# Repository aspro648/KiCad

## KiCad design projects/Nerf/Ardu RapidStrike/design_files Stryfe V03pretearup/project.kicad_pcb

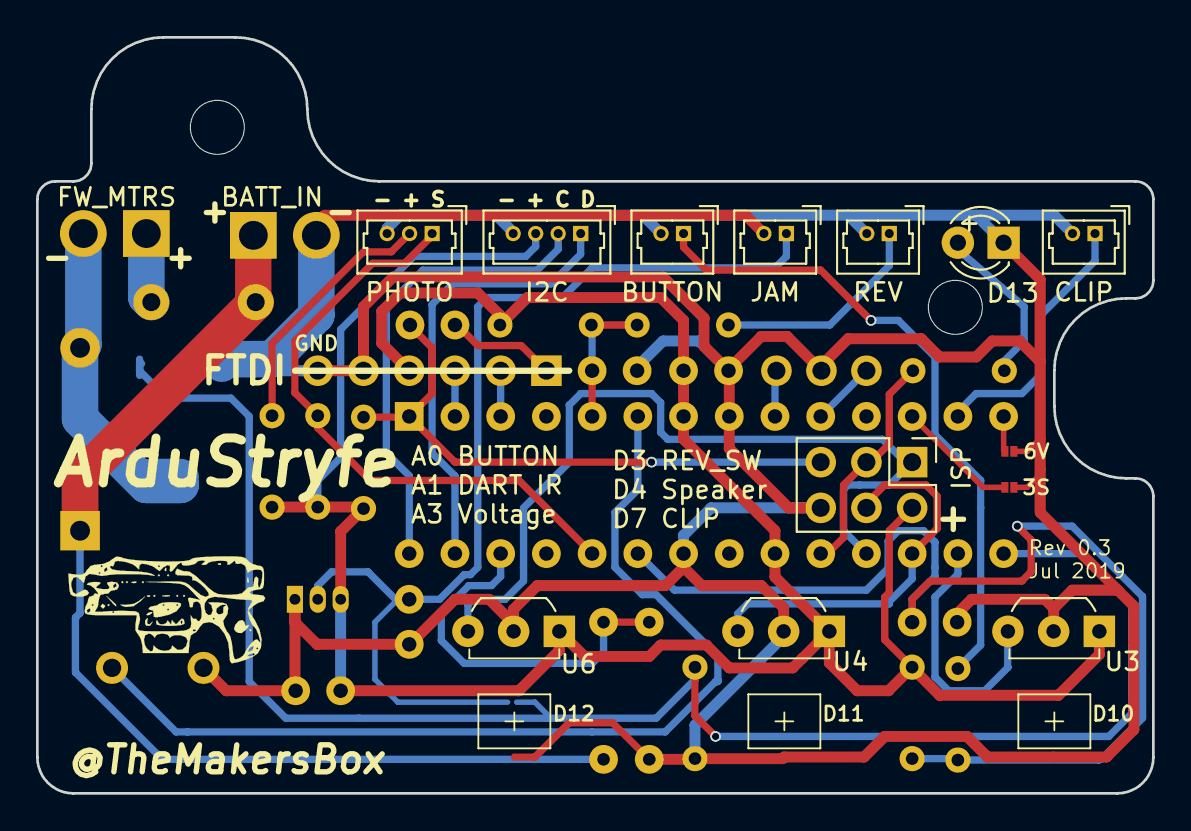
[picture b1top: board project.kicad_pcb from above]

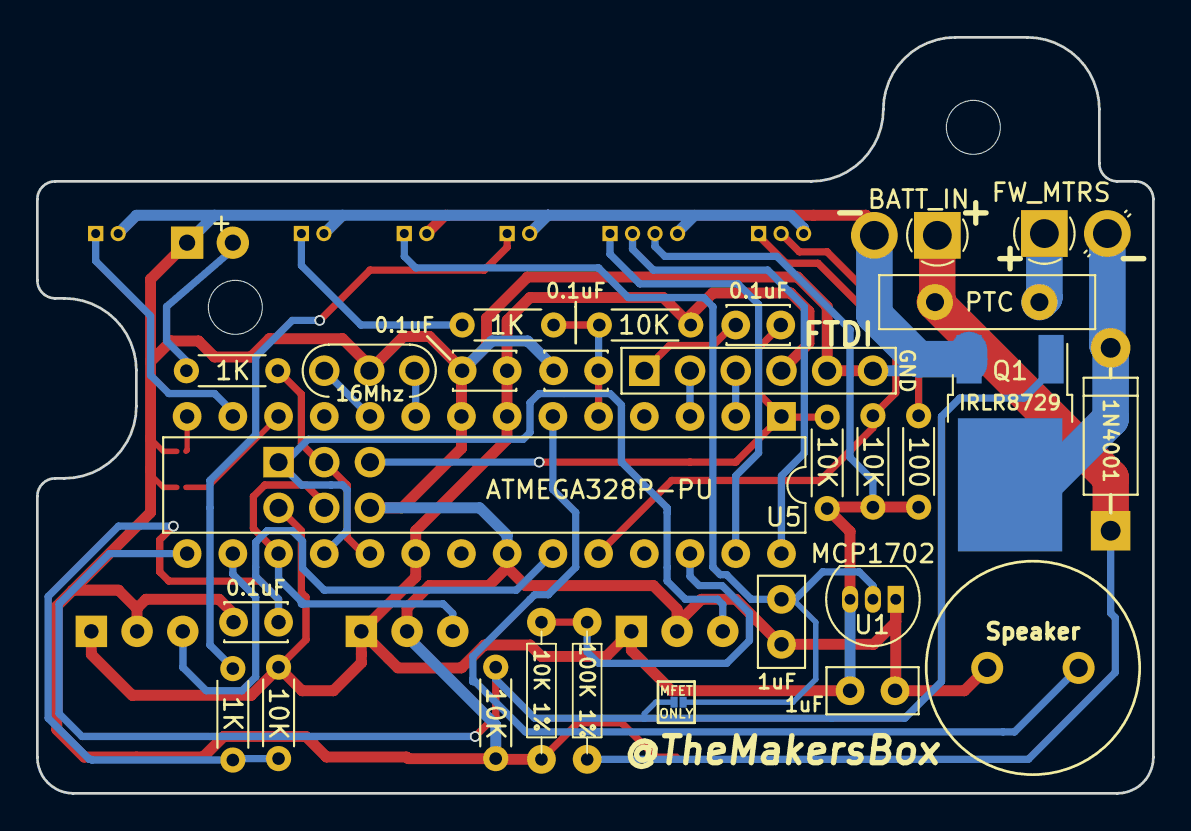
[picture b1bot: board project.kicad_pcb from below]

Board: 2 copper layers, 62.0 x 42.0 mm, 43 parts (28 on the bottom side), 31 nets.

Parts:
C1, C4: 1uF; C_Disc_D5.0mm_W2.5mm_P2.50mm
C5, C7, C9, C10: 0.1uF; C_Disc_D3.4mm_W2.1mm_P2.50mm
CON1: ISP; Pin_Header_Straight_2x03_Pitch2.54mm
D1: 1N4001; D_DO-41
D2: D13; LED_D3.0mm
F1: PTC; Fuse_Littelfuse-LVR125
J1: JAM; Molex_PicoBlade_53047-0210_02x1.25mm_Straight
J2: BATT_IN; TerminalBlock_P3.50mm_Horizontal
J5: I2C; Molex_PicoBlade_53047-0410_04x1.25mm_Straight
J6: REV; Molex_PicoBlade_53047-0210_02x1.25mm_Straight
J7: FTDI; Pin_Header_Straight_1x06_Pitch2.54mm
J8: PHOTO; Molex_PicoBlade_53047-0310_03x1.25mm_Straight
J9: FW_MTRS; TerminalBlock_P3.50mm_Horizontal
J12: CLIP; Molex_PicoBlade_53047-0210_02x1.25mm_Straight
J14, J14#2: NPTH; SolderWirePad_single_2-5mmDrill
J21: BUTTON; Molex_PicoBlade_53047-0210_02x1.25mm_Straight
JP1: 6V; JMP
JP2: 3S; JMP
JP3: MOSFET_ONLY; JMP
LS1: Speaker; SPEAKER
Q1: IRLR8729; TO-252-2_hand_soldering
R2, R7, R18: 1K; R__P5.08mm
R6, R9, R17, R19, R20: 10K; R__P5.08mm
R8: 100K 1%; R_7.5mm
R12: 10K 1%; R_7.5mm
R21: 100; R__P5.08mm
U1: MCP1702; TO-92_Inline_Narrow_Oval
U3, U4, U6: HALL SENSOR; Hall_Sensor
U5: ATMEGA328P-PU; DIP-28_W7.62mm
Y1: 16Mhz; Resonator-3pin_w7.0mm_h2.5mm

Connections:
/0(Rx): J7.3, U5.2
/1(Tx): J7.2, U5.3
/3(**): C7.1, R6.1, R7.2, U5.5
/4: LS1.1, U5.6
/6(**): JP2.1, U5.12
/7: J12.1, U5.13
/8: JP1.1, U5.14
/9(**): JP3.2, Q1.1, R9.2, U5.15
/10(SS): U3.3, U5.16
/11(MOSI): CON1.4, U4.3, U5.17
/12(MISO): CON1.1, U5.18, U6.3
/13(SCK): CON1.3, R2.1, U5.19
/#RTS: C9.1, J7.1
/A0: C10.1, R18.2, R19.1, U5.23
/A1: J8.1, R20.2, U5.24
/A3: R8.1, R12.1, U5.26
/A4(SDA): J5.1, U5.27
/A5(SCL): J5.2, U5.28
/BATT: D1.1, F1.1, J1.2, J2.1, R8.2
/Reset: C9.2, CON1.5, R17.1, U5.1
GND: C1.2, C4.2, C5.2, C7.2, C10.2, CON1.6, D2.1, J2.2, J5.4, J6.2, J7.5, J7.6, J8.3, J12.2, J21.2, JP1.2, JP2.2, LS1.2, Q1.3, R9.1, R12.2, U1.1, U3.2, U4.2, U5.8, U5.22, U6.2, Y1.2
unnamed: C1.1, J1.1, JP3.1, U1.2
unnamed: D1.2, J9.2, Q1.2
unnamed: D2.2, R2.2
unnamed: F1.2, J9.1
unnamed: J6.1, R7.1
unnamed: J8.2, R21.2
unnamed: J21.1, R18.1
unnamed: U5.9, Y1.3
unnamed: U5.10, Y1.1
VCC: C4.1, C5.1, CON1.2, J5.3, J7.4, R6.2, R17.2, R19.2, R20.1, R21.1, U1.3, U3.1, U4.1, U5.7, U5.20, U6.1

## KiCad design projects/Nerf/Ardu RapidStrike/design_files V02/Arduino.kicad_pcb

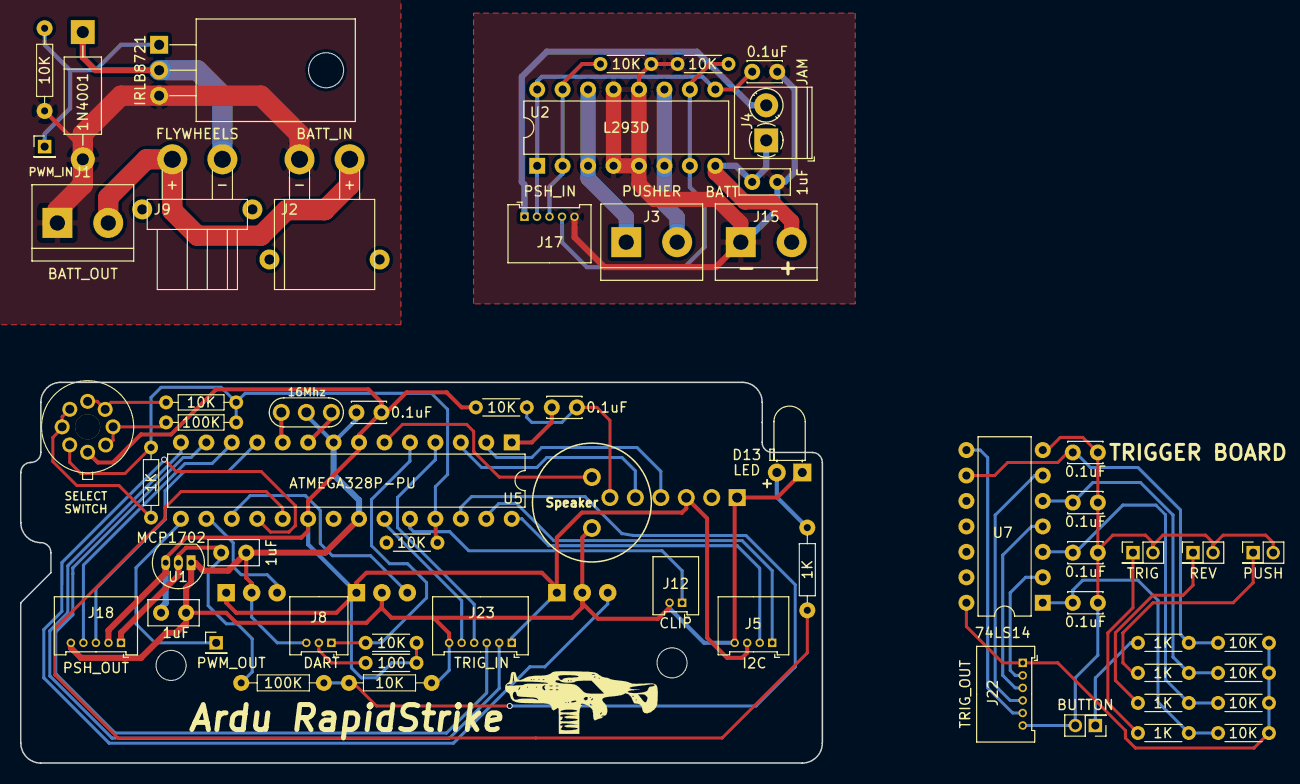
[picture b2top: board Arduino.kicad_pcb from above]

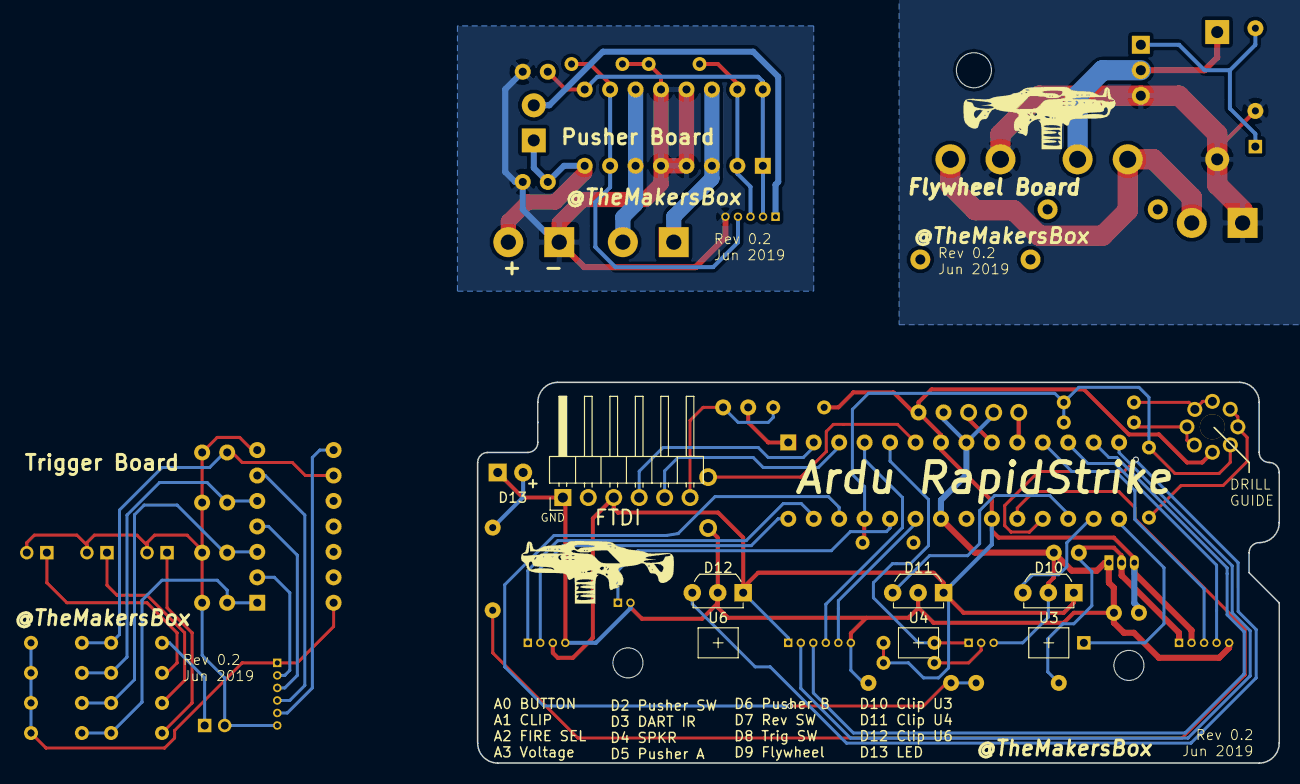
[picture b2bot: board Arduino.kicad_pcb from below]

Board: 2 copper layers, 80.0 x 38.0 mm, 67 parts (4 on the bottom side), 52 nets.

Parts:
C1, C2, C4: 1uF; C_Disc_D5.0mm_W2.5mm_P2.50mm
C3, C5, C6, C7, C8, C9, C10: 0.1uF; C_Disc_D3.4mm_W2.1mm_P2.50mm
D1: 1N4001; D_DO-15_P12.70mm_Horizontal
D2: D13; LED_D3.0mm_Horizontal_O1.27mm_Z10.0mm
J1: BATT_OUT; TerminalBlock_bornier-2_P5.08mm
J2: BATT_IN; XT30PW_M
J3: PUSHER; TerminalBlock_bornier-2_P5.08mm
J4: JAM; TerminalBlock_Phoenix_PT-1,5-2-3.5-H_1x02_P3.50mm_Horizontal
J5: I2C; Molex_PicoBlade_53048-0410_04x1.25mm_Angled
J6: REV; Pin_Header_Straight_2x01_Pitch2.00mm
J7: FTDI; Pin_Header_Angled_1x06_Pitch2.54mm
J8: DART; Molex_PicoBlade_53048-0310_03x1.25mm_Angled
J9: FLYWHEELS; XT30PW_F
J10: PWM_IN; Pin_Header_Straight_1x01_Pitch2.00mm
J11: PWM_OUT; Pin_Header_Straight_1x01_Pitch2.00mm
J12: CLIP; Molex_PicoBlade_53048-0210_02x1.25mm_Angled
J13, J14, J16: NPTH; SolderWirePad_single_2-5mmDrill
J15: BATT; TerminalBlock_bornier-2_P5.08mm
J17: PSH_IN; Molex_PicoBlade_53048-0510_05x1.25mm_Angled
J18: PSH_OUT; Molex_PicoBlade_53048-0510_05x1.25mm_Angled
J19: TRIG; Pin_Header_Straight_2x01_Pitch2.00mm
J20: PUSH; Pin_Header_Straight_2x01_Pitch2.00mm
J21: BUTTON; Pin_Header_Straight_2x01_Pitch2.00mm
J22: TRIG_OUT; Molex_PicoBlade_53048-0610_06x1.25mm_Angled
J23: TRIG_IN; Molex_PicoBlade_53048-0610_06x1.25mm_Angled
LS1: Speaker; SPEAKER
Q1: IRLB8721; TO-220-3_Horizontal
R1, R3, R4, R6, R10, R16, R17, R19, R20: 10K; R__P5.08mm
R2: 1K; R_Axial_DIN0204_L3.6mm_D1.6mm_P7.62mm_Horizontal
R5, R7, R11, R18: 1K; R__P5.08mm
R8: 100K; R_Axial_DIN0204_L3.6mm_D1.6mm_P7.62mm_Horizontal
R9, R12: 10K; R_Axial_DIN0204_L3.6mm_D1.6mm_P7.62mm_Horizontal
R13: 100K; R__P7mm
R14: 10K; R__P7mm
R15: 1K; R__P7mm
R21: 100; R__P5.08mm
SW1: SW_Rotary8
U1: MCP1702; TO-92_Inline_Narrow_Oval
U2: L293D; DIP-16_W7.62mm
U3, U4, U6: HALL SENSOR; Hall_Sensor
U5: ATMEGA328P-PU; DIP-28_W7.62mm
U7: 74LS14; DIP-14_W7.62mm
Y1: 16Mhz; Resonator-3pin_w7.0mm_h2.5mm

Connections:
/0(Rx): J7.4, U5.2
/1(Tx): J7.5, U5.3
/2: J23.4, U5.4
/3(**): J8.1, R20.2, U5.5
/4: LS1.1, U5.6
/5(**): J18.3, U5.11
/6(**): J18.4, U5.12
/7: J23.3, U5.13
/8: J23.2, U5.14
/9(**): J10.1, J11.1, Q1.1, R9.2, U5.15
/10(SS): U3.3, U5.16
/11(MOSI): U4.3, U5.17
/12(MISO): U5.18, U6.3
/13(SCK): R2.1, U5.19
/#RTS: C9.1, J7.6, R17.1
/A0: J23.5, U5.23
/A1: J12.1, U5.24
/A2: R13.1, R14.1, R15.1, R16.2, SW1.1, U5.25
/A3: R8.1, R12.1, U5.26
/A4(SDA): J5.1, U5.27
/A5(SCL): J5.2, U5.28
/BUTTON: J22.5, U7.8
/PUSHER: J22.4, U7.6
/REV: J22.3, U7.4
/Reset: C9.2, U5.1
/TRIG: J22.2, U7.2
/Vin: C1.1, J4.2, J17.1, J18.1, R8.2, U1.2
GND: C1.2, C2.2, C3.2, C4.2, C5.2, C6.2, C7.2, C8.2, C10.2, D1.2, D2.1, J1.1, J2.2, J5.4, J6.2, J7.1, J8.3, J12.2, J15.1, J17.5, J18.5, J19.2, J20.2, J21.2, J22.6, J23.6, LS1.2, Q1.3, R1.1, R3.1, R9.1, R12.2, R16.1, U1.1, U2.4, U2.5, U2.12, U2.13, U3.2, U4.2, U5.8, U5.22, U6.2, U7.7, Y1.2
unnamed: C2.1, J4.1, J15.2, U2.8
unnamed: C3.1, J17.2, U2.1, U2.9, U2.16
unnamed: C6.1, R4.1, R5.2, U7.1
unnamed: C7.1, R6.1, R7.2, U7.3
unnamed: C8.1, R10.1, R11.2, U7.5
unnamed: C10.1, R18.2, R19.1, U7.9
unnamed: D1.1, J9.2, Q1.2
unnamed: D2.2, R2.2
unnamed: J1.2, J2.1, J9.1
unnamed: J3.1, U2.3, U2.14
unnamed: J3.2, U2.6, U2.11
unnamed: J6.1, R7.1
unnamed: J8.2, R21.2
unnamed: J17.3, R1.2, U2.2, U2.15
unnamed: J17.4, R3.2, U2.7, U2.10
unnamed: J19.1, R5.1
unnamed: J20.1, R11.1
unnamed: J21.1, R18.1
unnamed: R13.2, SW1.6, SW1.7
unnamed: R14.2, SW1.4, SW1.5
unnamed: R15.2, SW1.2, SW1.3
unnamed: U5.9, Y1.3
unnamed: U5.10, Y1.1
VCC: C4.1, C5.1, J5.3, J7.3, J18.2, J22.1, J23.1, R4.2, R6.2, R10.2, R17.2, R19.2, R20.1, R21.1, SW1.8, U1.3, U3.1, U4.1, U5.7, U5.20, U6.1, U7.14
